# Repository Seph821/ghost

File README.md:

# ghost

# Build
`qmk compile -kb ghost -km default`

# Flash Left
`qmk flash -kb ghost -km default -bl uf2-split-left`

# Flash Right
`qmk flash -kb ghost -km default -bl uf2-split-right`

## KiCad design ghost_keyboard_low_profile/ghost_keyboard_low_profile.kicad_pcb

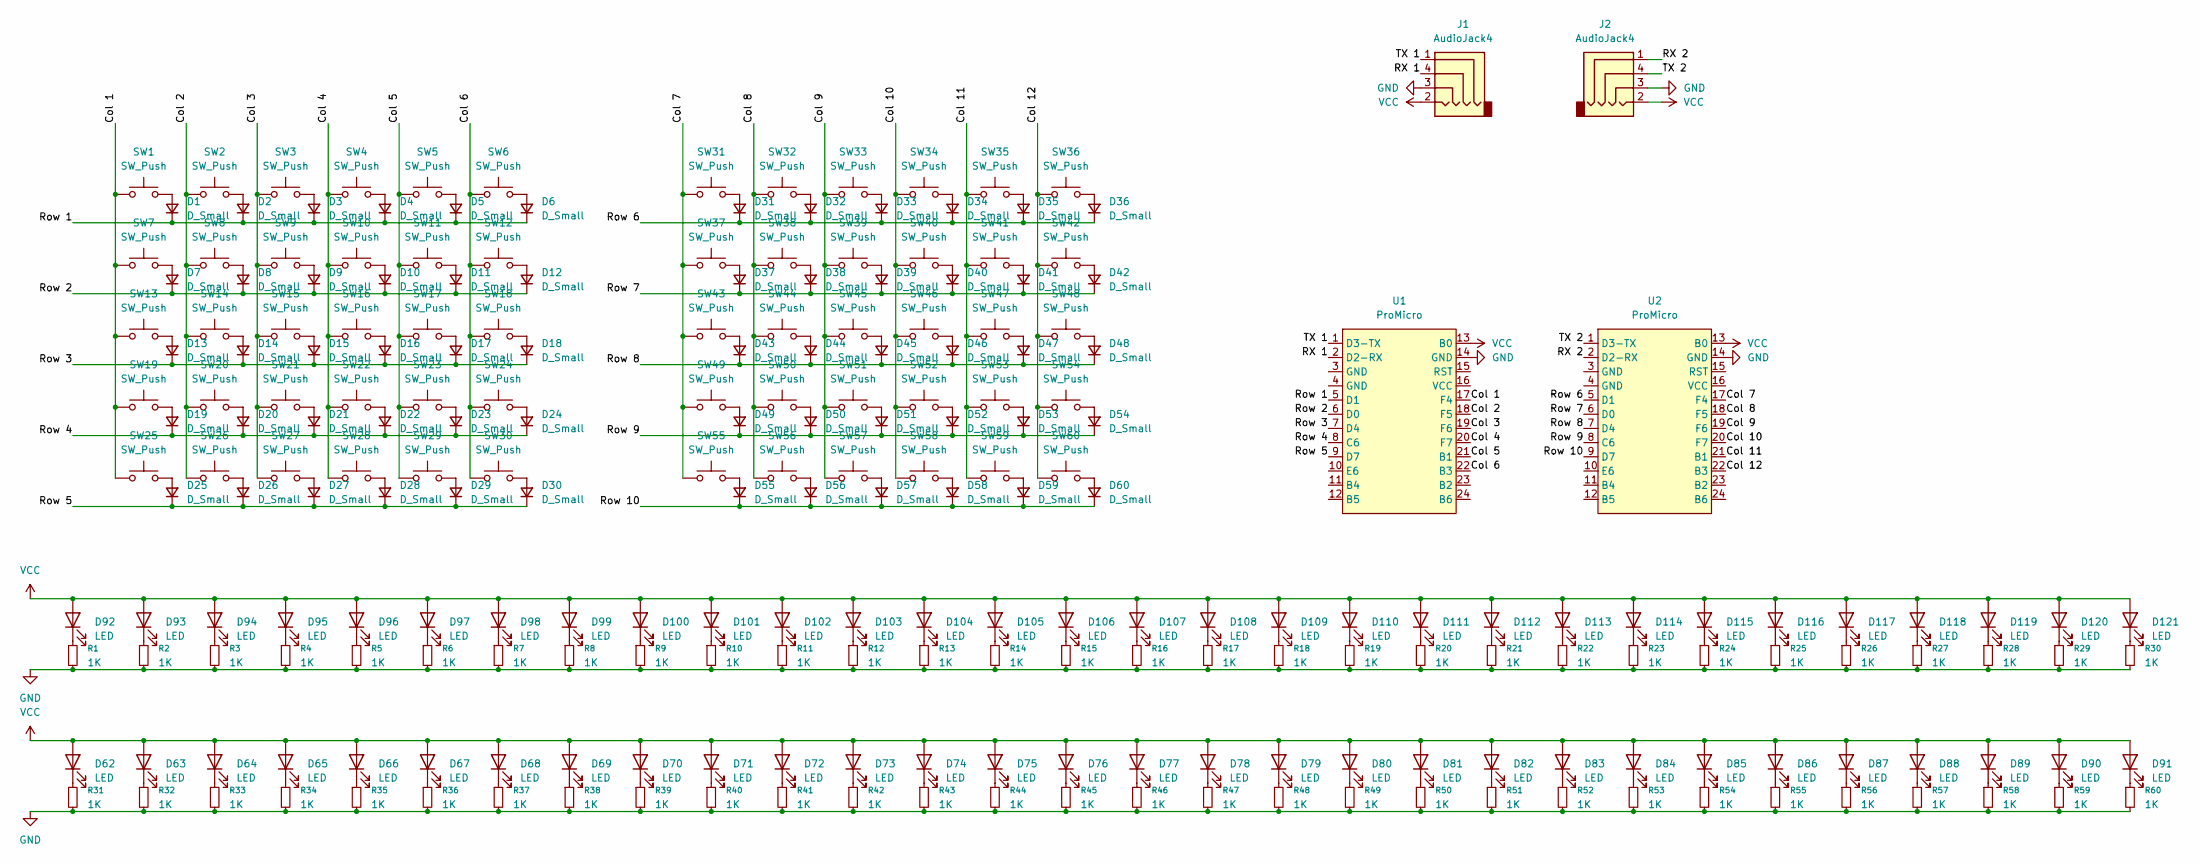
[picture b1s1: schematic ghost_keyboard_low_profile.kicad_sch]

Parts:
D1, D2, D3, D4, D5, D6, D7, D8, D9, D10, D11, D12, D13, D14, D15, D16, D17, D18, D19, D20, D21, D22, D23, D24, D25, D26, D27, D28, D29, D30, D31, D32, D33, D34, D35, D36, D37, D38, D39, D40, D41, D42, D43, D44, D45, D46, D47, D48, D49, D50, D51, D52, D53, D54, D55, D56, D57, D58, D59, D60: D_Small; D_SOD-123
D62, D63, D64, D65, D66, D67, D68, D69, D70, D71, D72, D73, D74, D75, D76, D77, D78, D79, D80, D81, D82, D83, D84, D85, D86, D87, D88, D89, D90, D91, D92, D93, D94, D95, D96, D97, D98, D99, D100, D101, D102, D103, D104, D105, D106, D107, D108, D109, D110, D111, D112, D113, D114, D115, D116, D117, D118, D119, D120, D121: LED; LED_1206_3216Metric_ReverseMount_Hole1.8x2.4mm
J1, J2: AudioJack4; TRRS-PJ-320A
R1, R2, R3, R4, R5, R6, R7, R8, R9, R10, R11, R12, R13, R14, R15, R16, R17, R18, R19, R20, R21, R22, R23, R24, R25, R26, R27, R28, R29, R30, R31, R32, R33, R34, R35, R36, R37, R38, R39, R40, R41, R42, R43, R44, R45, R46, R47, R48, R49, R50, R51, R52, R53, R54, R55, R56, R57, R58, R59, R60: 1K; R_1206_3216Metric_Pad1.30x1.75mm_HandSolder
SW1, SW2, SW3, SW4, SW5, SW6, SW7, SW8, SW9, SW10, SW11, SW12, SW13, SW14, SW15, SW16, SW17, SW18, SW19, SW20, SW21, SW22, SW23, SW24, SW25, SW26, SW27, SW28, SW29, SW30, SW31, SW32, SW33, SW34, SW35, SW36, SW37, SW38, SW39, SW40, SW41, SW42, SW43, SW44, SW45, SW46, SW47, SW48, SW49, SW50, SW51, SW52, SW53, SW54, SW55, SW56, SW57, SW58, SW59, SW60: SW_Push; SW_Gateron_LowProfile_HotSwap_PTH
U1, U2: ProMicro; ProMicro_USBup

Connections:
/Col 1: SW1.1, SW7.1, SW13.1, SW19.1, SW25.1, U1.17 (F4)
/Col 2: SW2.1, SW8.1, SW14.1, SW20.1, SW26.1, U1.18 (F5)
/Col 3: SW3.1, SW9.1, SW15.1, SW21.1, SW27.1, U1.19 (F6)
/Col 4: SW4.1, SW10.1, SW16.1, SW22.1, SW28.1, U1.20 (F7)
/Col 5: SW5.1, SW11.1, SW17.1, SW23.1, SW29.1, U1.21 (B1)
/Col 6: SW6.1, SW12.1, SW18.1, SW24.1, SW30.1, U1.22 (B3)
/Col 7: SW31.1, SW37.1, SW43.1, SW49.1, SW55.1, U2.17 (F4)
/Col 8: SW32.1, SW38.1, SW44.1, SW50.1, SW56.1, U2.18 (F5)
/Col 9: SW33.1, SW39.1, SW45.1, SW51.1, SW57.1, U2.19 (F6)
/Col 10: SW34.1, SW40.1, SW46.1, SW52.1, SW58.1, U2.20 (F7)
/Col 11: SW35.1, SW41.1, SW47.1, SW53.1, SW59.1, U2.21 (B1)
/Col 12: SW36.1, SW42.1, SW48.1, SW54.1, SW60.1, U2.22 (B3)
/RX 1: J1.4, U1.2 (D2-RX)
/RX 2: J2.1, U2.2 (D2-RX)
/Row 1: D1.1 (K), D2.1 (K), D3.1 (K), D4.1 (K), D5.1 (K), D6.1 (K), U1.5 (D1)
/Row 2: D7.1 (K), D8.1 (K), D9.1 (K), D10.1 (K), D11.1 (K), D12.1 (K), U1.6 (D0)
/Row 3: D13.1 (K), D14.1 (K), D15.1 (K), D16.1 (K), D17.1 (K), D18.1 (K), U1.7 (D4)
/Row 4: D19.1 (K), D20.1 (K), D21.1 (K), D22.1 (K), D23.1 (K), D24.1 (K), U1.8 (C6)
/Row 5: D25.1 (K), D26.1 (K), D27.1 (K), D28.1 (K), D29.1 (K), D30.1 (K), U1.9 (D7)
/Row 6: D31.1 (K), D32.1 (K), D33.1 (K), D34.1 (K), D35.1 (K), D36.1 (K), U2.5 (D1)
/Row 7: D37.1 (K), D38.1 (K), D39.1 (K), D40.1 (K), D41.1 (K), D42.1 (K), U2.6 (D0)
/Row 8: D43.1 (K), D44.1 (K), D45.1 (K), D46.1 (K), D47.1 (K), D48.1 (K), U2.7 (D4)
/Row 9: D49.1 (K), D50.1 (K), D51.1 (K), D52.1 (K), D53.1 (K), D54.1 (K), U2.8 (C6)
/Row 10: D55.1 (K), D56.1 (K), D57.1 (K), D58.1 (K), D59.1 (K), D60.1 (K), U2.9 (D7)
/TX 1: J1.1, U1.1 (D3-TX)
/TX 2: J2.4, U2.1 (D3-TX)
GND: J1.3, J2.3, R1.2, R2.2, R3.2, R4.2, R5.2, R6.2, R7.2, R8.2, R9.2, R10.2, R11.2, R12.2, R13.2, R14.2, R15.2, R16.2, R17.2, R18.2, R19.2, R20.2, R21.2, R22.2, R23.2, R24.2, R25.2, R26.2, R27.2, R28.2, R29.2, R30.2, R31.2, R32.2, R33.2, R34.2, R35.2, R36.2, R37.2, R38.2, R39.2, R40.2, R41.2, R42.2, R43.2, R44.2, R45.2, R46.2, R47.2, R48.2, R49.2, R50.2, R51.2, R52.2, R53.2, R54.2, R55.2, R56.2, R57.2, R58.2, R59.2, R60.2, U1.14 (GND), U2.14 (GND)
unnamed: D1.2 (A), SW1.2
unnamed: D2.2 (A), SW2.2
unnamed: D3.2 (A), SW3.2
unnamed: D4.2 (A), SW4.2
unnamed: D5.2 (A), SW5.2
unnamed: D6.2 (A), SW6.2
unnamed: D7.2 (A), SW7.2
unnamed: D8.2 (A), SW8.2
unnamed: D9.2 (A), SW9.2
unnamed: D10.2 (A), SW10.2
unnamed: D11.2 (A), SW11.2
unnamed: D12.2 (A), SW12.2
unnamed: D13.2 (A), SW13.2
unnamed: D14.2 (A), SW14.2
unnamed: D15.2 (A), SW15.2
unnamed: D16.2 (A), SW16.2
unnamed: D17.2 (A), SW17.2
unnamed: D18.2 (A), SW18.2
unnamed: D19.2 (A), SW19.2
unnamed: D20.2 (A), SW20.2
unnamed: D21.2 (A), SW21.2
unnamed: D22.2 (A), SW22.2
unnamed: D23.2 (A), SW23.2
unnamed: D24.2 (A), SW24.2
unnamed: D25.2 (A), SW25.2
unnamed: D26.2 (A), SW26.2
unnamed: D27.2 (A), SW27.2
unnamed: D28.2 (A), SW28.2
unnamed: D29.2 (A), SW29.2
unnamed: D30.2 (A), SW30.2
unnamed: D31.2 (A), SW31.2
unnamed: D32.2 (A), SW32.2
unnamed: D33.2 (A), SW33.2
unnamed: D34.2 (A), SW34.2
unnamed: D35.2 (A), SW35.2
unnamed: D36.2 (A), SW36.2
unnamed: D37.2 (A), SW37.2
unnamed: D38.2 (A), SW38.2
unnamed: D39.2 (A), SW39.2
unnamed: D40.2 (A), SW40.2
unnamed: D41.2 (A), SW41.2
unnamed: D42.2 (A), SW42.2
unnamed: D43.2 (A), SW43.2
unnamed: D44.2 (A), SW44.2
unnamed: D45.2 (A), SW45.2
unnamed: D46.2 (A), SW46.2
unnamed: D47.2 (A), SW47.2
unnamed: D48.2 (A), SW48.2
unnamed: D49.2 (A), SW49.2
unnamed: D50.2 (A), SW50.2
unnamed: D51.2 (A), SW51.2
unnamed: D52.2 (A), SW52.2
unnamed: D53.2 (A), SW53.2
unnamed: D54.2 (A), SW54.2
unnamed: D55.2 (A), SW55.2
unnamed: D56.2 (A), SW56.2
unnamed: D57.2 (A), SW57.2
unnamed: D58.2 (A), SW58.2
unnamed: D59.2 (A), SW59.2
unnamed: D60.2 (A), SW60.2
unnamed: D62.1 (K), R31.1
unnamed: D63.1 (K), R32.1
unnamed: D64.1 (K), R33.1
unnamed: D65.1 (K), R34.1
unnamed: D66.1 (K), R35.1
unnamed: D67.1 (K), R36.1
unnamed: D68.1 (K), R37.1
unnamed: D69.1 (K), R38.1
unnamed: D70.1 (K), R39.1
unnamed: D71.1 (K), R40.1
unnamed: D72.1 (K), R41.1
unnamed: D73.1 (K), R42.1
unnamed: D74.1 (K), R43.1
unnamed: D75.1 (K), R44.1
unnamed: D76.1 (K), R45.1
unnamed: D77.1 (K), R46.1
unnamed: D78.1 (K), R47.1
unnamed: D79.1 (K), R48.1
unnamed: D80.1 (K), R49.1
unnamed: D81.1 (K), R50.1
unnamed: D82.1 (K), R51.1
unnamed: D83.1 (K), R52.1
unnamed: D84.1 (K), R53.1
unnamed: D85.1 (K), R54.1
unnamed: D86.1 (K), R55.1
unnamed: D87.1 (K), R56.1
unnamed: D88.1 (K), R57.1
unnamed: D89.1 (K), R58.1
unnamed: D90.1 (K), R59.1
unnamed: D91.1 (K), R60.1
unnamed: D92.1 (K), R1.1
unnamed: D93.1 (K), R2.1
unnamed: D94.1 (K), R3.1
unnamed: D95.1 (K), R4.1
unnamed: D96.1 (K), R5.1
unnamed: D97.1 (K), R6.1
unnamed: D98.1 (K), R7.1
unnamed: D99.1 (K), R8.1
unnamed: D100.1 (K), R9.1
unnamed: D101.1 (K), R10.1
unnamed: D102.1 (K), R11.1
unnamed: D103.1 (K), R12.1
unnamed: D104.1 (K), R13.1
unnamed: D105.1 (K), R14.1
unnamed: D106.1 (K), R15.1
unnamed: D107.1 (K), R16.1
unnamed: D108.1 (K), R17.1
unnamed: D109.1 (K), R18.1
unnamed: D110.1 (K), R19.1
unnamed: D111.1 (K), R20.1
unnamed: D112.1 (K), R21.1
unnamed: D113.1 (K), R22.1
unnamed: D114.1 (K), R23.1
unnamed: D115.1 (K), R24.1
unnamed: D116.1 (K), R25.1
unnamed: D117.1 (K), R26.1
unnamed: D118.1 (K), R27.1
unnamed: D119.1 (K), R28.1
unnamed: D120.1 (K), R29.1
unnamed: D121.1 (K), R30.1
VCC: D62.2 (A), D63.2 (A), D64.2 (A), D65.2 (A), D66.2 (A), D67.2 (A), D68.2 (A), D69.2 (A), D70.2 (A), D71.2 (A), D72.2 (A), D73.2 (A), D74.2 (A), D75.2 (A), D76.2 (A), D77.2 (A), D78.2 (A), D79.2 (A), D80.2 (A), D81.2 (A), D82.2 (A), D83.2 (A), D84.2 (A), D85.2 (A), D86.2 (A), D87.2 (A), D88.2 (A), D89.2 (A), D90.2 (A), D91.2 (A), D92.2 (A), D93.2 (A), D94.2 (A), D95.2 (A), D96.2 (A), D97.2 (A), D98.2 (A), D99.2 (A), D100.2 (A), D101.2 (A), D102.2 (A), D103.2 (A), D104.2 (A), D105.2 (A), D106.2 (A), D107.2 (A), D108.2 (A), D109.2 (A), D110.2 (A), D111.2 (A), D112.2 (A), D113.2 (A), D114.2 (A), D115.2 (A), D116.2 (A), D117.2 (A), D118.2 (A), D119.2 (A), D120.2 (A), D121.2 (A), J1.2, J2.2, U1.13 (B0), U2.13 (B0)

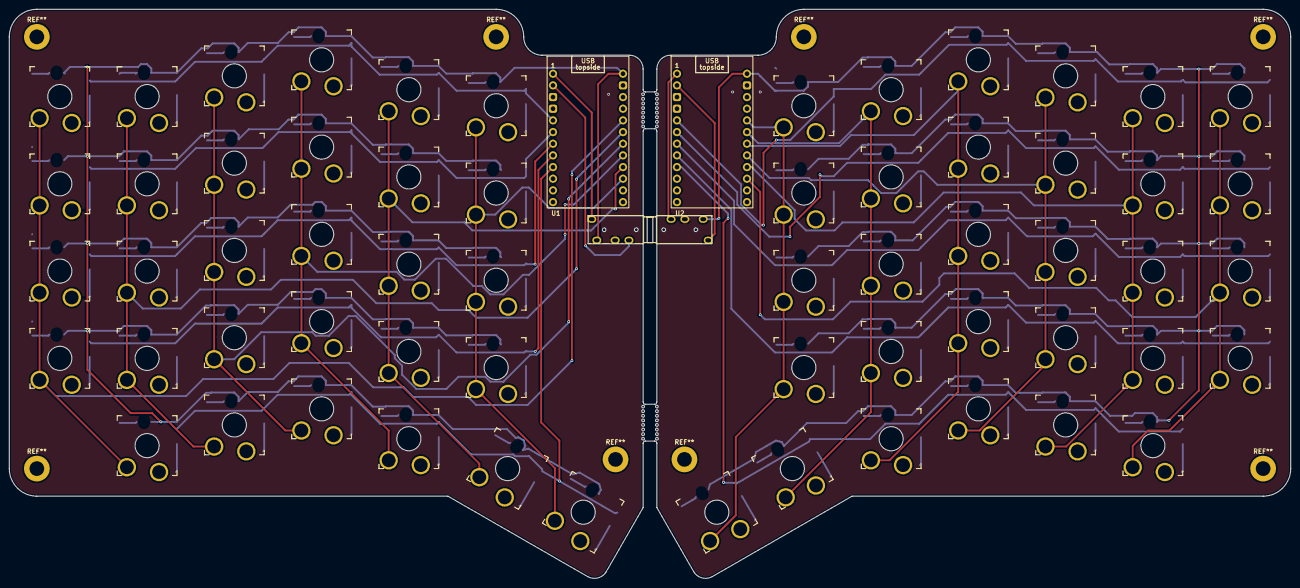
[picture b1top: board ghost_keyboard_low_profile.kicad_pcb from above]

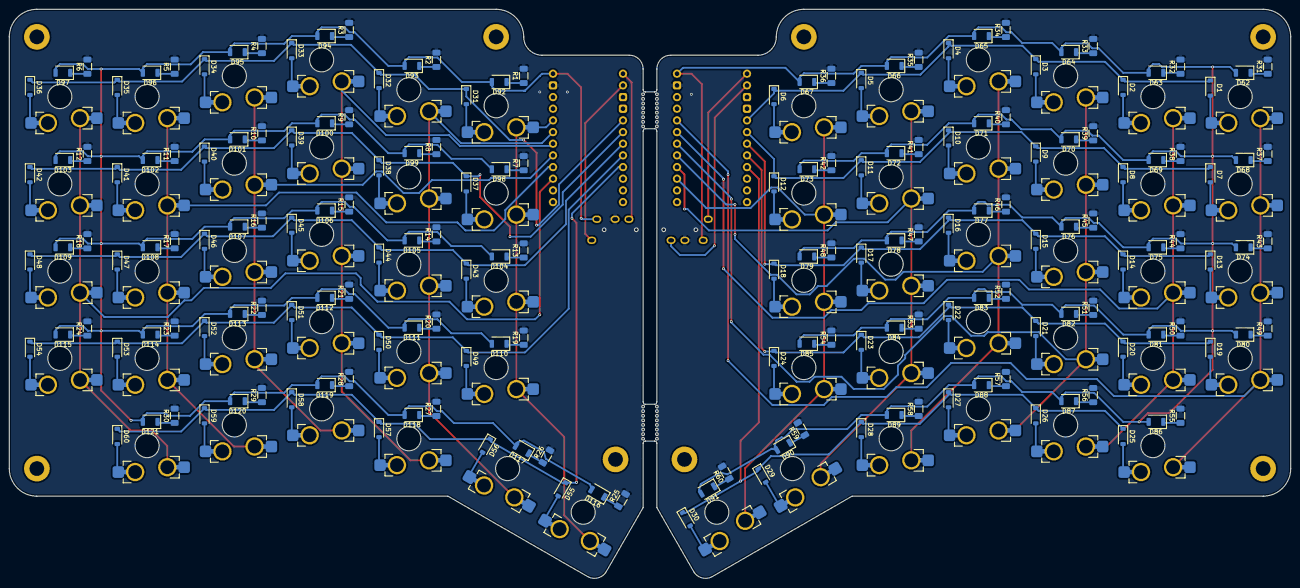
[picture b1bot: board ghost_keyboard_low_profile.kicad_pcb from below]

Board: 2 copper layers, 279.0 x 123.9 mm, 244 parts (180 on the bottom side), 148 nets.
